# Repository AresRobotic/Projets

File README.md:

Projets
=======

Dépot servant à centraliser les documents de tout types de projets des membres d'ARES

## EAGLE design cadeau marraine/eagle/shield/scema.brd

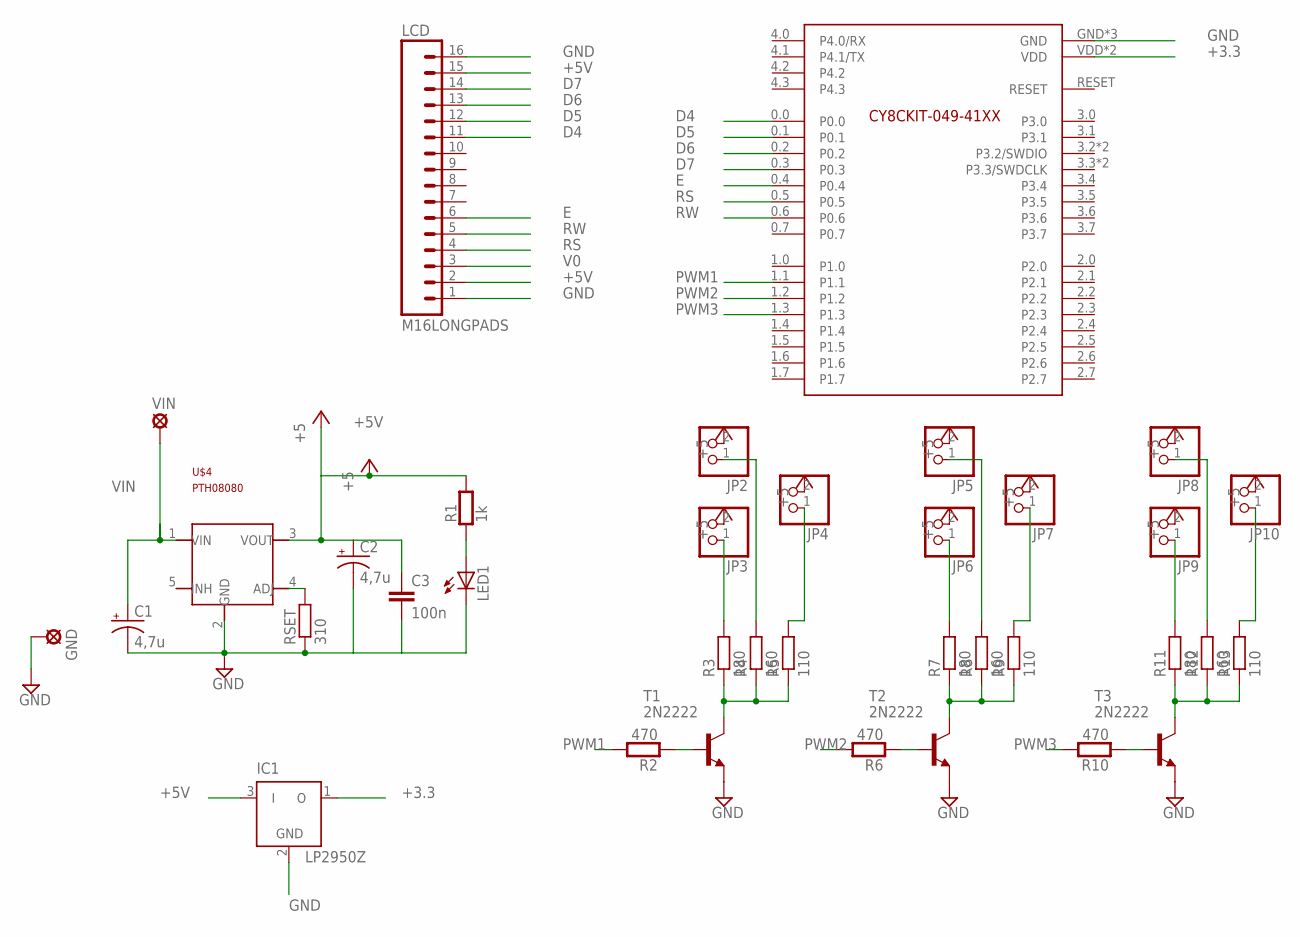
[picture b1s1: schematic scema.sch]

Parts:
C1, C2: 4,7u; CPOL-RADIAL-10UF-25V
C3: 100n; CAP-PTH-SMALL2
GND: SE14
IC1: LP2950Z; TO92
JP2, JP3, JP4, JP5, JP6, JP7, JP8, JP9, JP10: PINHD-1X2; 1X02
LCD: M16LONGPADS; 1X16_LONGPADS
LED1: LEDSML0805; SML0805
R1: 1k; 0805
R2, R6, R10: 470; 0805
R3, R7, R11: 180; 0207/12
R4, R8, R12: 160; 0207/12
R5, R9, R13: 110; 0207/12
RSET: 310; R0805
T1, T2, T3: 2N2222; TO18
U$1: PSOC4DEV; CY8CKIT-049-41XX
U$4: PTH08080; PTH08080EUF
VIN: SE14

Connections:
+3.3: IC1.1 (O), U$1.VDD, U$1.VDD2 (VDD)
+5V: C2.1 (+), C3.1, IC1.3 (I), JP2.2, JP3.2, JP4.2, JP5.2, JP6.2, JP7.2, JP8.2, JP9.2, JP10.2, LCD.2, LCD.15, R1.2, U$4.3 (VOUT)
D4: LCD.11, U$1.0.0
D5: LCD.12, U$1.0.1
D6: LCD.13, U$1.0.2
D7: LCD.14, U$1.0.3
E: LCD.6, U$1.0.4
GND: C1.2 (-), C2.2 (-), C3.2, GND.MP, IC1.2 (GND), LCD.1, LCD.16, LED1.C, RSET.1, T1.1 (E), T2.1 (E), T3.1 (E), U$1.GND, U$1.GND1 (GND), U$1.GND2 (GND), U$4.2 (GND)
unnamed: R2.1, T1.2 (B)
unnamed: R6.1, T2.2 (B)
unnamed: RSET.2, U$4.4 (ADJ)
unnamed: JP3.1, R3.2
unnamed: R3.1, R4.1, R5.1, T1.3 (C)
unnamed: JP2.1, R4.2
unnamed: JP4.1, R5.2
unnamed: JP6.1, R7.2
unnamed: R7.1, R8.1, R9.1, T2.3 (C)
unnamed: LED1.A, R1.1
unnamed: JP5.1, R8.2
unnamed: JP7.1, R9.2
unnamed: R10.1, T3.2 (B)
unnamed: JP9.1, R11.2
unnamed: R11.1, R12.1, R13.1, T3.3 (C)
unnamed: JP8.1, R12.2
unnamed: JP10.1, R13.2
PWM1: R2.2, U$1.1.1
PWM2: R6.2, U$1.1.2
PWM3: R10.2, U$1.1.3
RS: LCD.4, U$1.0.5
RW: LCD.5, U$1.0.6
V0: LCD.3
VIN: C1.1 (+), U$4.1 (VIN), VIN.MP

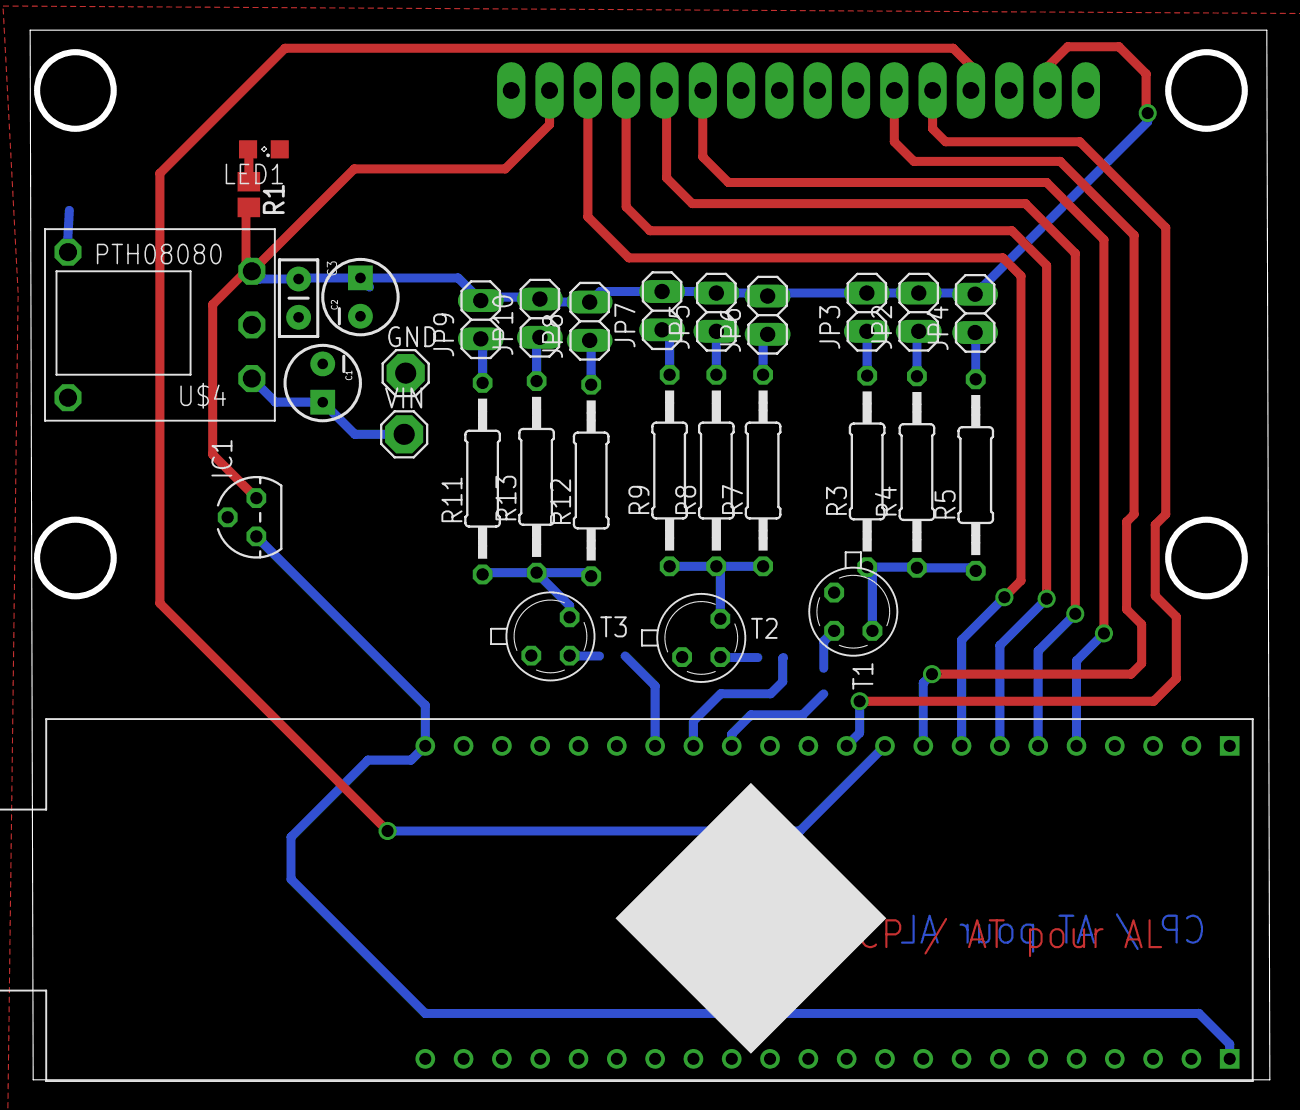
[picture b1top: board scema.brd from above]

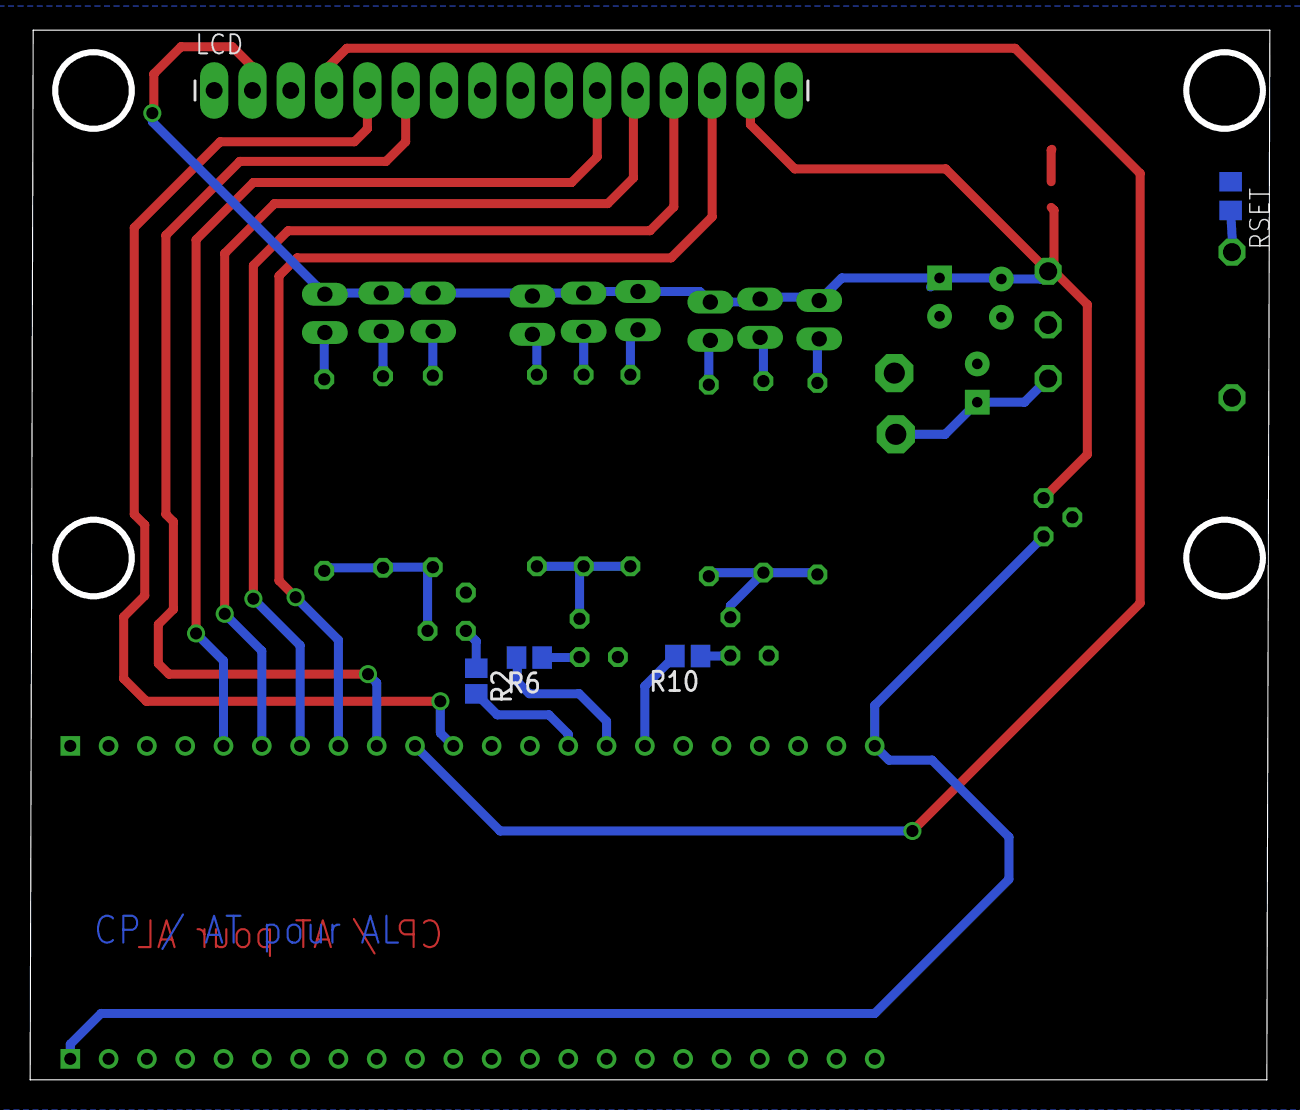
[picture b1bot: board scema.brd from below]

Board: 2 copper layers, 81.8 x 69.2 mm, 36 parts (5 on the bottom side), 31 nets.

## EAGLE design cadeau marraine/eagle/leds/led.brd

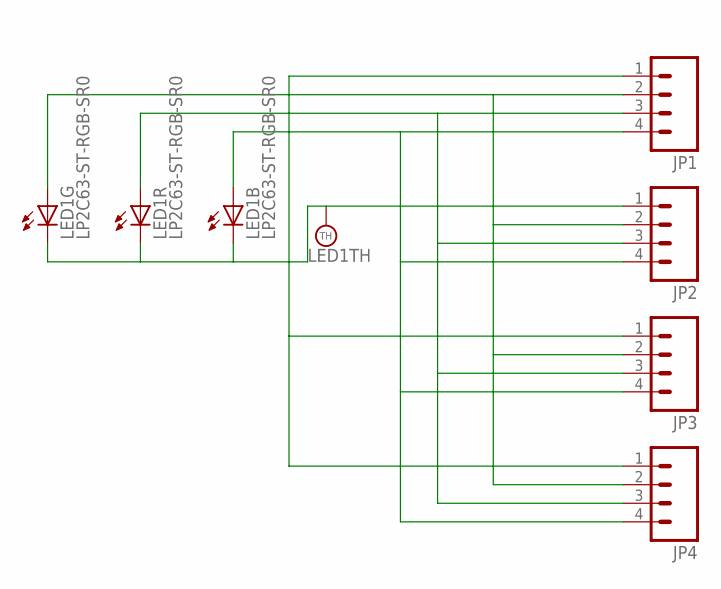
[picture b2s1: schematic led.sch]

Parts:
JP1, JP2, JP3, JP4: M04LONGPADS; 1X04_LONGPADS
LED1: LP2C63-ST-RGB-SR0

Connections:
GND: JP1.1, JP2.1, JP3.1, JP4.1, LED1.4 (C), LED1.5 (C), LED1.6 (C)
unnamed: JP1.4, JP2.4, JP3.4, JP4.4, LED1.3 (A)
unnamed: JP1.3, JP2.3, JP3.3, JP4.3, LED1.2 (A)
unnamed: JP1.2, JP2.2, JP3.2, JP4.2, LED1.1 (A)

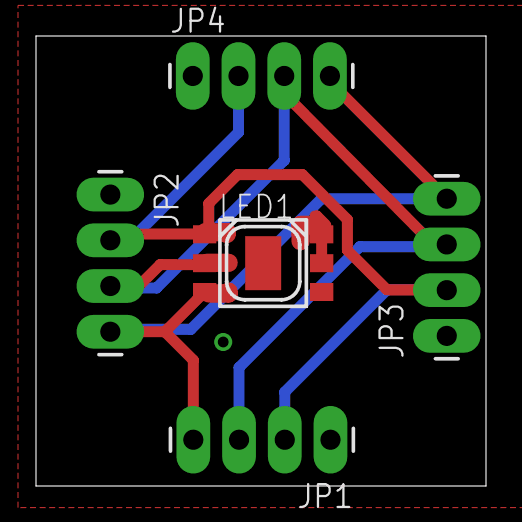
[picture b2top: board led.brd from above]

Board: 2 copper layers, 25.0 x 25.0 mm, 5 parts (0 on the bottom side), 4 nets.

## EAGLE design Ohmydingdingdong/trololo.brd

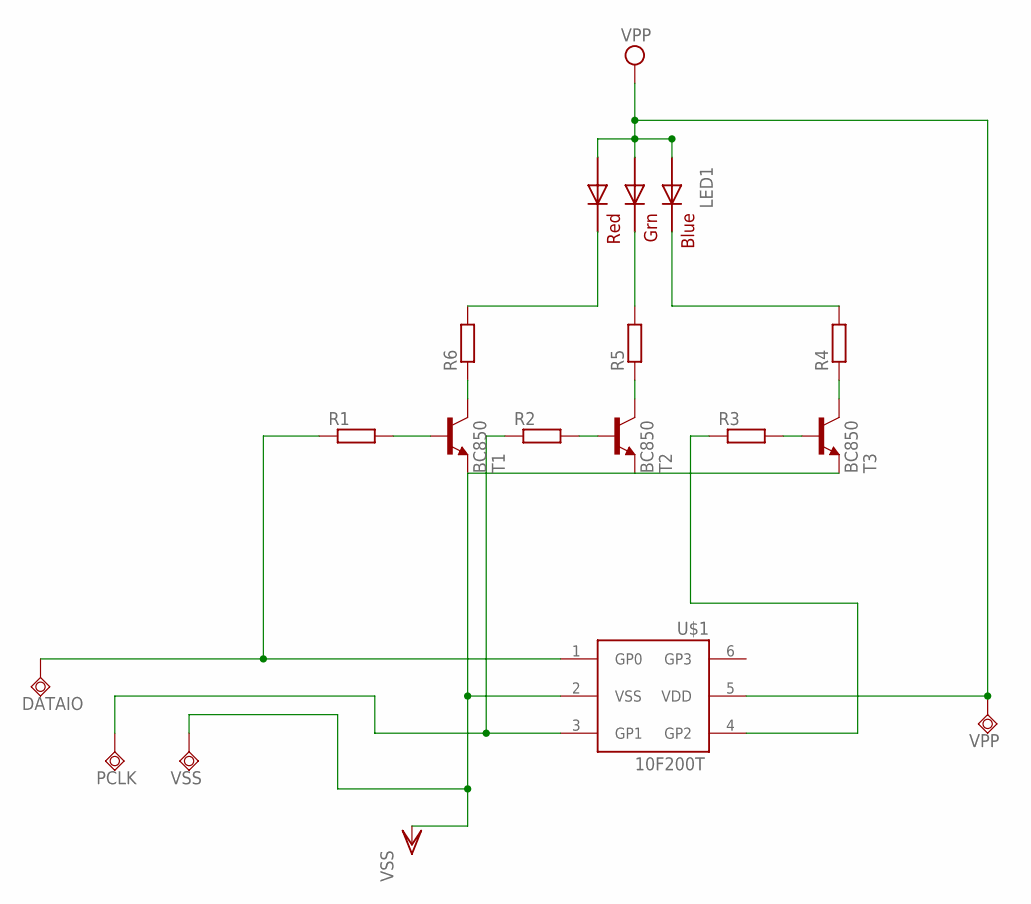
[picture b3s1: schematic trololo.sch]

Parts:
DATAIO: TPSQPAD1-20Y; P1-20Y
LED1: RGBLED5050
PCLK: TPSQPAD1-20Y; P1-20Y
R1, R2, R3, R4, R5, R6: R-EU_R0805; R0805
T1, T2, T3: BC850; SOT23
U$1: 10F200T; SOT23-6
VPP: TPSQPAD1-20Y; P1-20Y
VSS: TPSQPAD1-20Y; P1-20Y

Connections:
unnamed: R5.1, T2.3 (C)
unnamed: R4.1, T3.3 (C)
unnamed: R6.1, T1.3 (C)
unnamed: R1.2, T1.1 (B)
unnamed: R2.2, T2.1 (B)
unnamed: R3.2, T3.1 (B)
unnamed: DATAIO.TP, R1.1, U$1.1 (GP0)
unnamed: PCLK.TP, R2.1, U$1.3 (GP1)
unnamed: R3.1, U$1.4 (GP2)
unnamed: LED1.5 (RED_C), R6.2
unnamed: LED1.6 (GREEN_C), R5.2
unnamed: LED1.4 (BLUE_C), R4.2
VPP: LED1.1 (GREEN_A), LED1.2 (RED_A), LED1.3 (BLUE_A), U$1.5 (VDD), VPP.TP
VSS: T1.2 (E), T2.2 (E), T3.2 (E), U$1.2 (VSS), VSS.TP

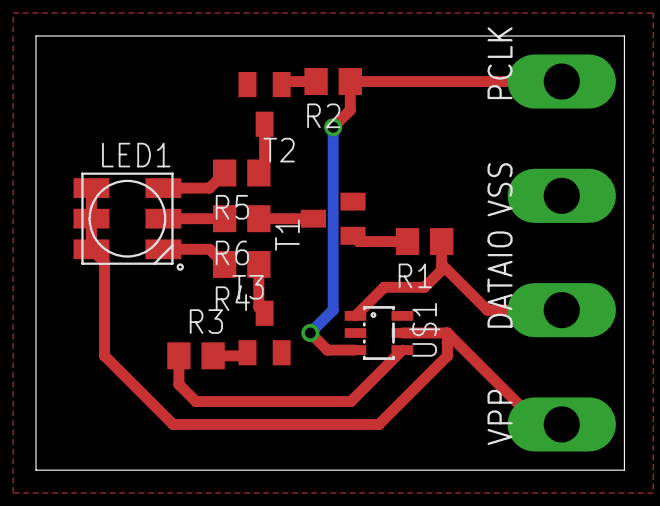
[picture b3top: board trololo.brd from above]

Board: 2 copper layers, 32.7 x 24.1 mm, 15 parts (0 on the bottom side), 14 nets.

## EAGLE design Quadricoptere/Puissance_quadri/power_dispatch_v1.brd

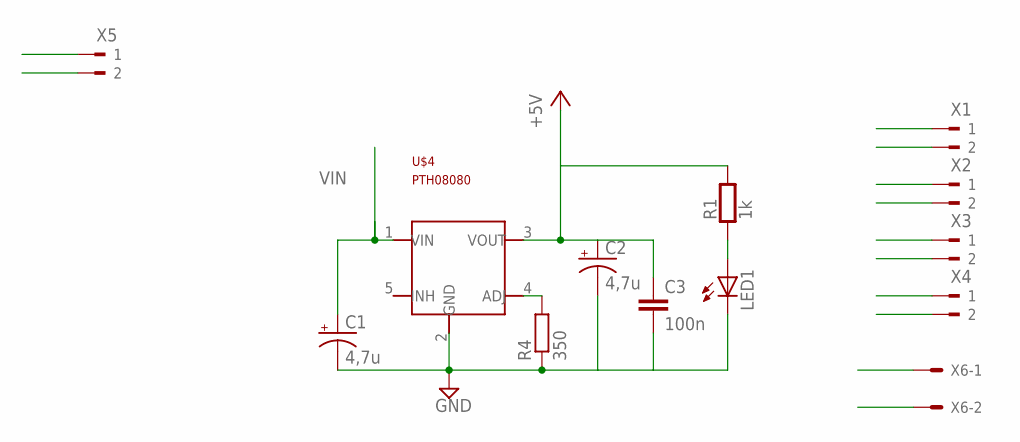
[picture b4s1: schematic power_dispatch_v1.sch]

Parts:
C1, C2: 4,7u; CPOL-RADIAL-10UF-25V
C3: 100n; CAP-PTH-SMALL2
LED1: LEDSML0805; SML0805
R1: 1k; 0805
R4: 350; R0805
U$4: PTH08080; PTH08080EUF
X1, X2, X3, X4, X5: 90-2
X6: KK-156-2

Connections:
+5V: C2.1 (+), C3.1, R1.2, U$4.3 (VOUT), X6.1
GND: C1.2 (-), C2.2 (-), C3.2, LED1.C, R4.1, U$4.2 (GND), X1.2, X2.2, X3.2, X4.2, X5.2, X6.2
unnamed: R4.2, U$4.4 (ADJ)
unnamed: LED1.A, R1.1
VIN: C1.1 (+), U$4.1 (VIN), X1.1, X2.1, X3.1, X4.1, X5.1

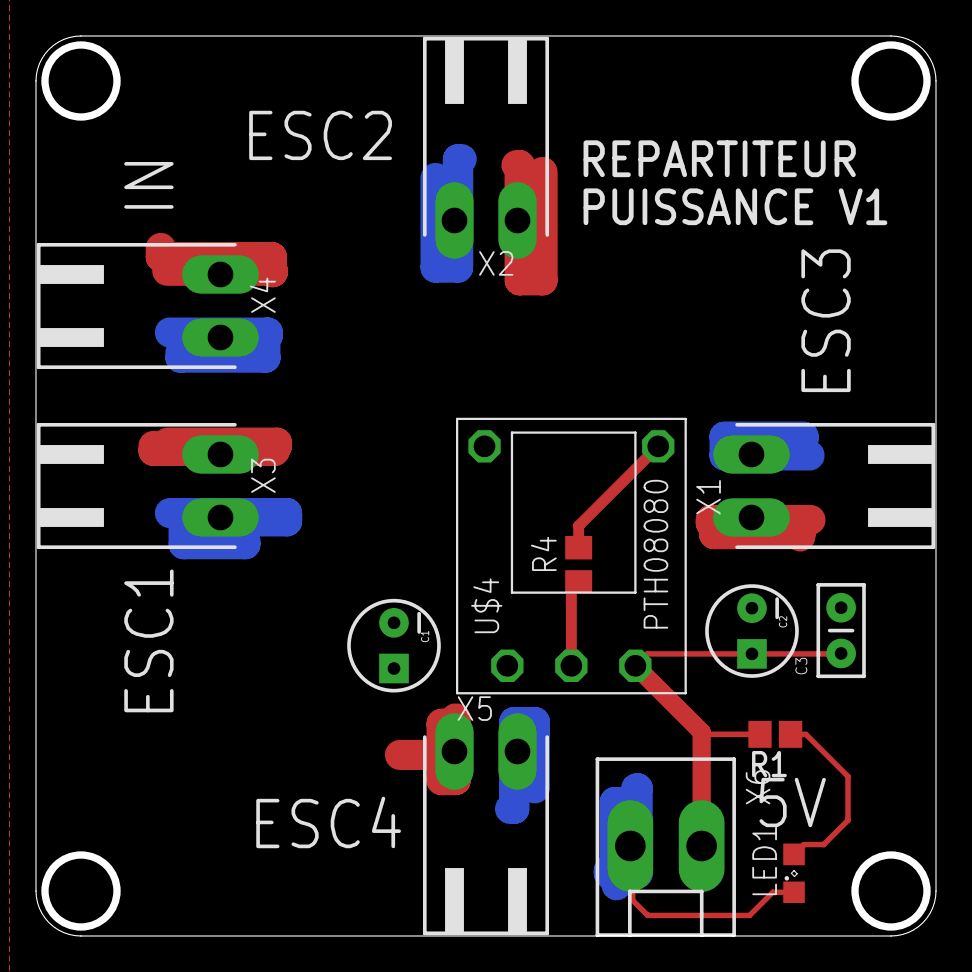
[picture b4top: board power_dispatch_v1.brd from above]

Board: 2 copper layers, 49.6 x 49.6 mm, 13 parts (0 on the bottom side), 5 nets.

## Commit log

2014-06-26 ajout de la carte de répartition puissance vers ESC et commande
2014-06-27 modification carte quadricoptere
2014-08-24 conception boitier quadri
    base modulaire v1
2014-08-26 modification base,
    problème dimension clipsage 2mm de trop .
    ajout du stl
2014-10-28 ajout différent projets
2014-10-28 new commit
2014-10-29 Ajout fichiers projet marraine promo 2017
2014-11-23 maj projet marraine
    maj projet psoc
2014-11-23 ajout modèle 3d
2014-11-24 déplacer carte alim dans robot 2015

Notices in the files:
parts and their libraries:
SparkFun-Passives: Licensing: CC v3.0 Share-Alike You are welcome to use this library for commercial purposes.
